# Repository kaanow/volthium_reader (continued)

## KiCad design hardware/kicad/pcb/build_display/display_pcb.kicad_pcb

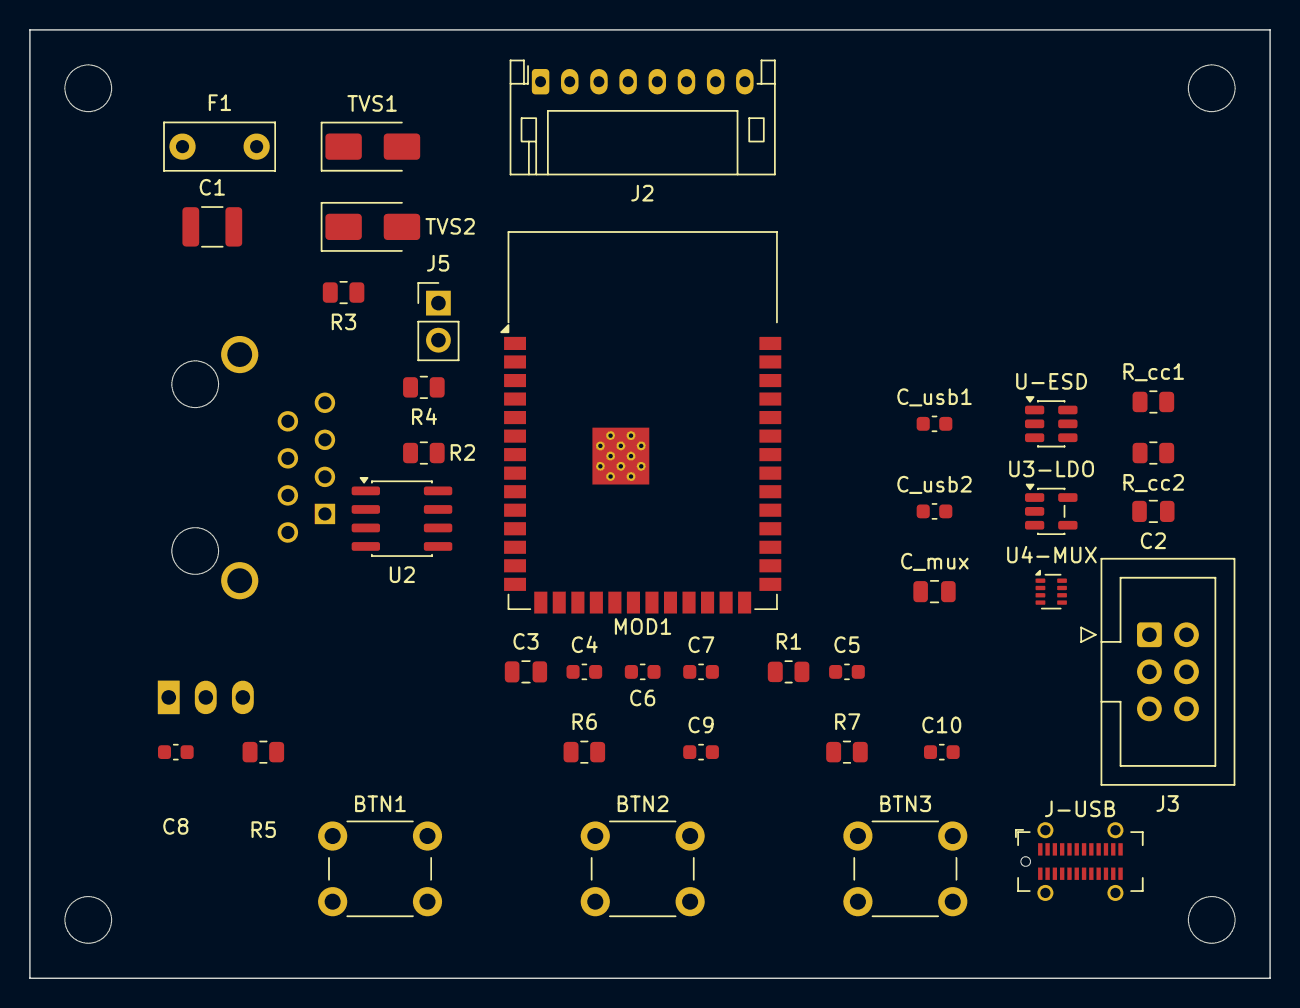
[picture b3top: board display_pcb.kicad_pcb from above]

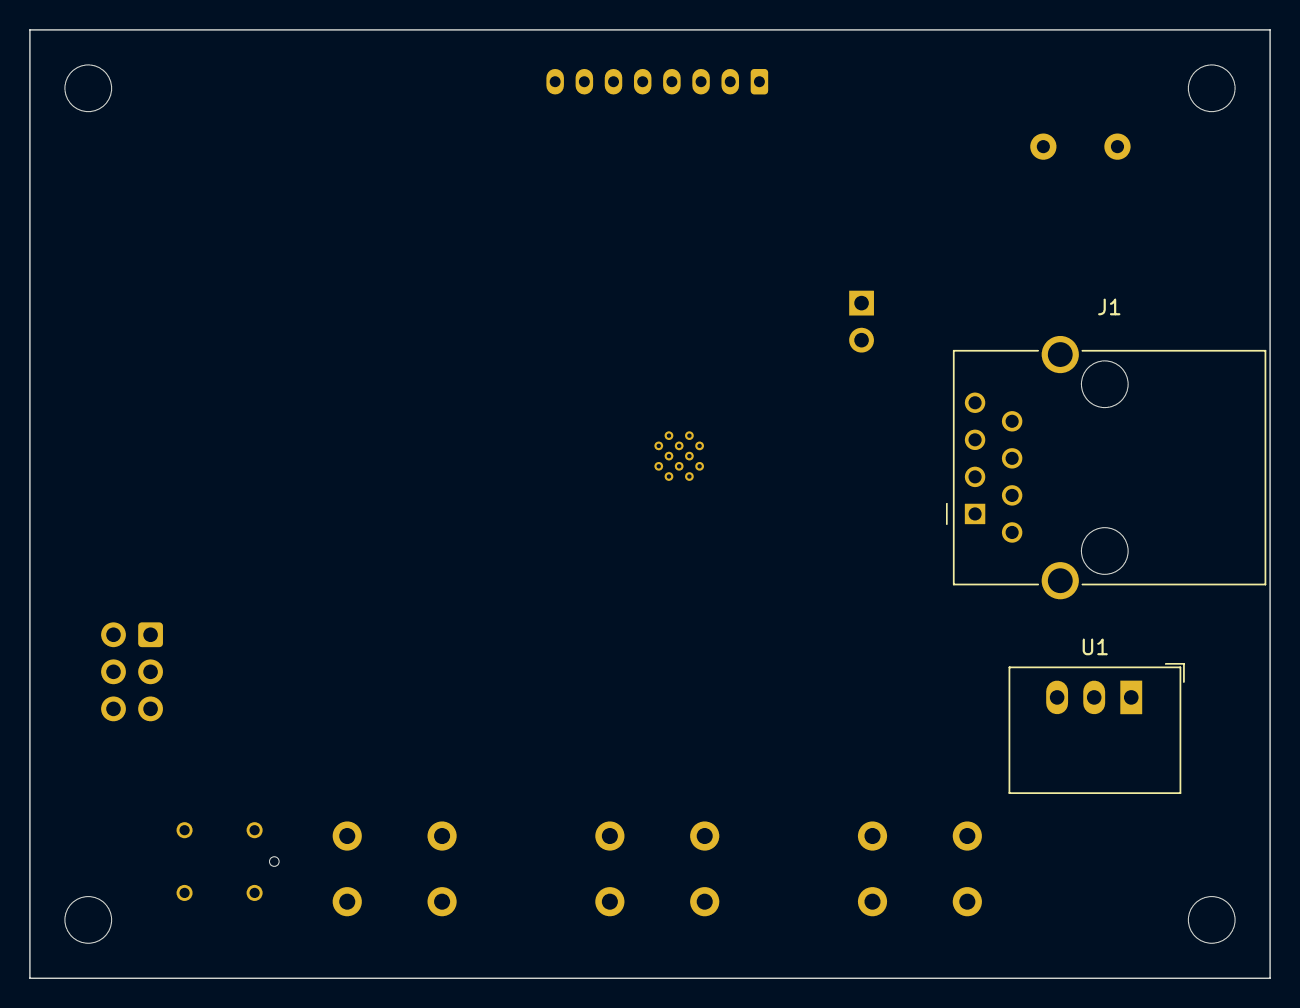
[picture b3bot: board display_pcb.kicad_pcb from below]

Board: 2 copper layers, 85.0 x 65.0 mm, 43 parts (2 on the bottom side), 31 nets, no tracks yet.

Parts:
BTN1, BTN2, BTN3: 6x6 tall-actuator; SW_PUSH_6mm_H13mm
C1: 22µF 25V; C_1210_3225Metric
C2, C3: 10µF; C_0805_2012Metric
C4, C7, C8, C9, C10: 100nF; C_0603_1608Metric
C5, C6: 1µF; C_0603_1608Metric
C_mux: 47µF; C_0805_2012Metric
C_usb1, C_usb2: 1µF; C_0603_1608Metric
F1: MF-R025; Fuse_Bourns_MF-R025_THT_P5.08mm
H1, H2, H3, H4: M3; MountingHole_3.2mm_M3
J1: Wurth_615008145521; J_Wurth_WR-MJ_615008145521
J2: JST_S8B-PH-K-S; JST_PH_S8B-PH-K_1x08_P2.00mm_Horizontal
J3: ESP-Prog; IDC-Header_2x03_P2.54mm_Vertical
J5: TERM; PinHeader_1x02_P2.54mm_Vertical
J-USB: USB4115-03-C; USB_C_Receptacle_GCT_USB4115-03-C
MOD1: ESP32-S3-WROOM-1-N16R8; ESP32-S3-WROOM-1_HSvia0.3_NoAntKeepout
R1: 10k; R_0805_2012Metric
R2: 120; R_0805_2012Metric
R3, R4: 330; R_0805_2012Metric
R5, R6, R7: 1M; R_0805_2012Metric
R_cc1, R_cc2: 5.1k; R_0805_2012Metric
TVS1: SMAJ15A-13-F; D_SMA
TVS2: SMAJ12CA-13-F; D_SMA
U1: R-78E3.3-0.5; Converter_DCDC_RECOM_R-78E-0.5_THT
U2: THVD1400DR; SOIC-8_3.9x4.9mm_P1.27mm
U3-LDO: AP2112K-3.3; SOT-23-5
U4-MUX: TPS2116DRLR; SOT-583-8
U-ESD: USBLC6-2SC6Y; SOT-23-6

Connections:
BOOT: J3.6, MOD1.27
BTN1_IN: BTN1.1, C8.1, MOD1.20, R5.2
BTN2_IN: BTN2.1, C9.1, MOD1.21, R6.2
BTN3_IN: BTN3.1, C10.1, MOD1.22, R7.2
DBG_RXD: J3.5, MOD1.36
DBG_TXD: J3.3, MOD1.37
EPD_BUSY: J2.8, MOD1.12
EPD_CS: J2.5, MOD1.5
EPD_DC: J2.6, MOD1.6
EPD_RST: J2.7, MOD1.7
GND: BTN1.2, BTN2.2, BTN3.2, C1.2, C2.2, C3.1, C4.1, C5.2, C6.2, C7.2, C8.2, C9.2, C10.2, C_mux.2, C_usb1.2, C_usb2.2, J1.6, J1.7, J1.8, J2.2, J3.4, J-USB.A1, J-USB.A12, J-USB.B1, J-USB.B12, J-USB.SH, MOD1.1, MOD1.40, MOD1.41, R4.2, R_cc1.2, R_cc2.2, TVS1.1, U1.2, U2.5, U3-LDO.2, U4-MUX.1, U-ESD.2
MCU_EN: C5.1, J3.1, MOD1.3, R1.2
unnamed: J5.1, R2.2
unnamed: J-USB.A5, R_cc1.1
unnamed: J-USB.B5, R_cc2.1
unnamed: C_usb2.1, U3-LDO.5, U4-MUX.3, U4-MUX.4, U4-MUX.5
RS485_A: J1.4, R2.1, R3.2, TVS2.2, U2.6
RS485_B: J1.5, J5.2, R4.1, TVS2.1, U2.7
RS485_DE: MOD1.38, U2.3
RS485_DI: MOD1.10, U2.4
RS485_RO: MOD1.11, U2.1
RS485_nRE: MOD1.8, U2.2
SPI_MOSI: J2.3, MOD1.18
SPI_SCK: J2.4, MOD1.17
USB_DM: J-USB.A7, J-USB.B7, MOD1.13, U-ESD.3
USB_DP: J-USB.A6, J-USB.B6, MOD1.14, U-ESD.1
V3V3: C3.2, C4.2, C6.1, C7.1, C_mux.1, J2.1, J3.2, MOD1.2, R1.1, R3.1, R5.1, R6.1, R7.1, U2.8, U4-MUX.2, U4-MUX.7
V3V3_REG: C2.1, U1.3, U4-MUX.6
V12_CAT5E: F1.1, J1.1, J1.2, J1.3
V12_PROT: C1.1, F1.2, TVS1.2, U1.1
VBUS: C_usb1.1, J-USB.A4, J-USB.A9, J-USB.B4, J-USB.B9, U3-LDO.1, U3-LDO.3, U-ESD.5

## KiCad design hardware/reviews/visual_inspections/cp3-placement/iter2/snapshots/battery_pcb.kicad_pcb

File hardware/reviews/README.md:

# `hardware/reviews/` — checkpoint review packets

Each PCB-design checkpoint produces a review packet here. Reviewers
(human or agent) start from the packet, follow links into the design
docs, and post findings as comments / commits / PR suggestions.

> **The standing standard is [`SOP.md`](SOP.md)** — the distilled gates,
> principles, and tooling every checkpoint must satisfy, forward-looking and
> free of the incident history. Read it before starting any CP. Role
> playbooks: [`DESIGNER.md`](DESIGNER.md), [`REVIEWER.md`](REVIEWER.md).

| File                            | Phase                | Status     |
|---------------------------------|----------------------|------------|
| `cp1_design_baseline.md`         | Design baseline      | **in review (re-opened, D18/D19)** |
| `cp2_schematic_capture.md`       | Schematic capture    | not started (next) |
| `cp3_placement.md`               | Footprint placement (battery) | not started |
| `cp4_display_placement.md`       | Footprint placement (display) | not started |
| `cp5_routing_drc.md`             | Routing + DRC        | not started |
| `cp6_fab_ready.md`               | Fab-ready package    | not started |

> **Note (2026-06-18):** CP1 was re-opened (decisions.md **D18**) after the
> engineering-correctness gate (D17) found CP1/CP2 architecture defects that
> had ridden to "CP6 fab-ready". The **prior CP2–CP6 review packets** (and
> the CP6 visual-inspection crops) describe board work built on the
> pre-D19 schematics and are **superseded** — they now live in
> [`archive/`](archive/) for history. New CP2+ packets will be written
> fresh against the corrected D19 design.

## What a review packet contains

Each packet is a single markdown file with:

1. **Status banner** — checkpoint name, date opened, current state
2. **What changed since the last checkpoint** — diff summary (commits, file list)
3. **What to look at** — pointers into the design docs + KiCad files,
   with the specific questions to evaluate
4. **Known unknowns / open decisions** — questions Claude is asking the
   reviewer to settle
5. **Success criteria** — what the reviewer needs to see to mark this
   checkpoint passed
6. **Reviewer findings** — appended by the reviewer; iterates until
   findings are resolved

## How to drive a review cycle

1. Claude commits the work and writes the packet
2. User triggers the reviewer (separate agent or human)
3. Reviewer appends findings to the packet
4. Claude addresses findings; updates packet with responses
5. Cycle continues until reviewer marks checkpoint passed
6. Next checkpoint begins

The reviewer is expected to read the packet only, not chase down design
decisions across the repo unless flagged. Claude's job is to make the
review packet self-contained.

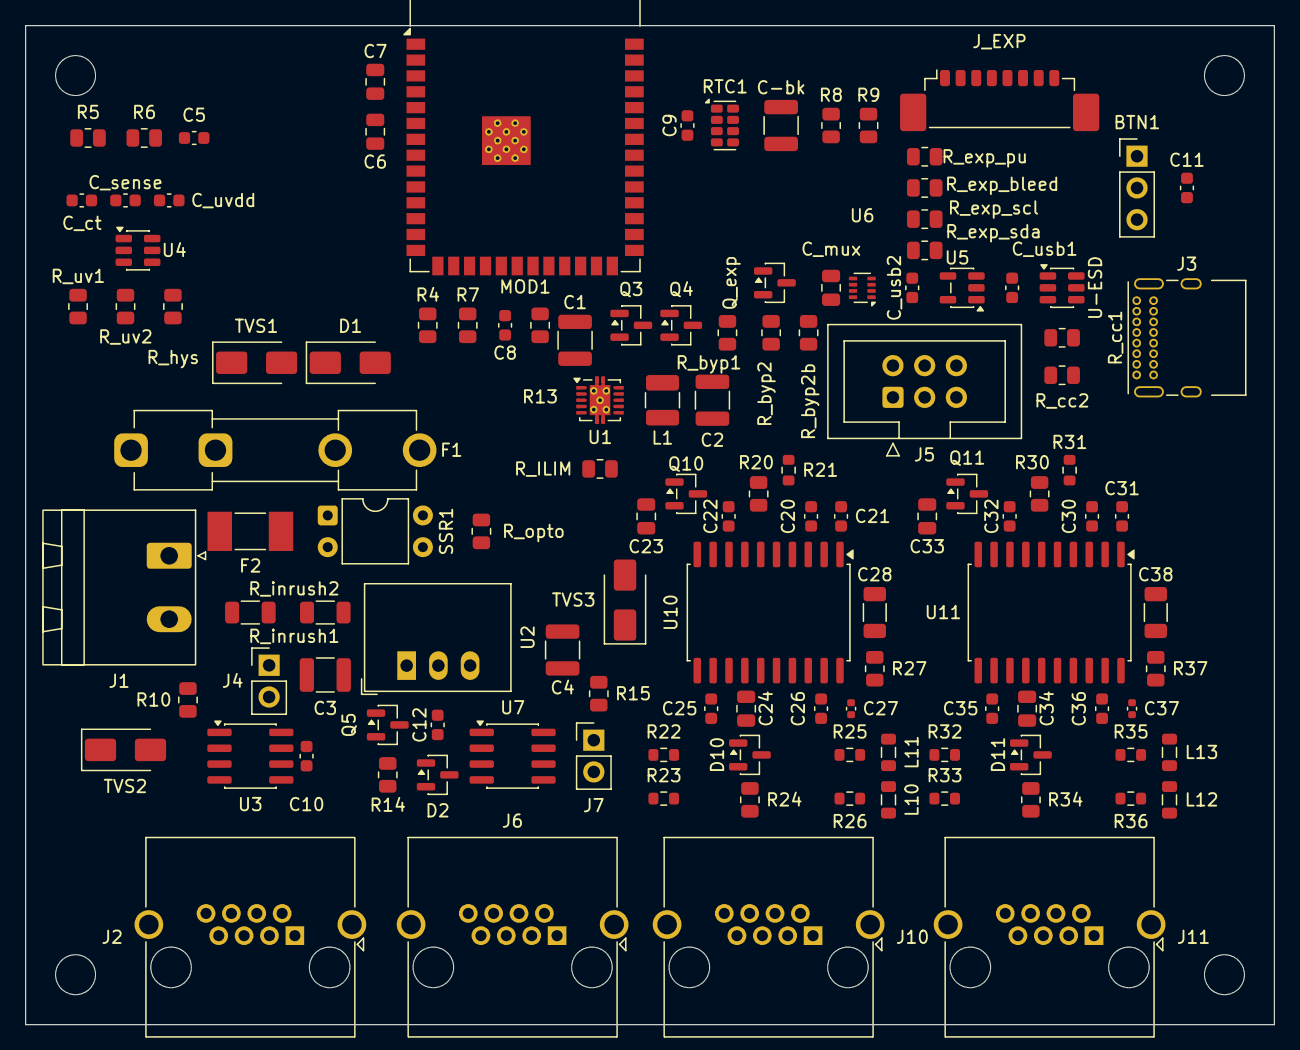
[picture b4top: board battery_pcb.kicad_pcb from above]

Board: 2 copper layers, 100.0 x 80.0 mm, 127 parts (0 on the bottom side), 84 nets, no tracks yet.

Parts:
BTN1: C&K_8125SHZBE; PinHeader_1x03_P2.54mm_Vertical
C1: 22µF 100V; C_1210_3225Metric
C2: 47µF 25V; C_1210_3225Metric
C3: 3.3µF 100V; C_1210_3225Metric
C4: 22µF 25V; C_1210_3225Metric
C5, C9, C10, C11, C12: 100nF; C_0603_1608Metric
C6, C23, C24, C33, C34: 10µF; C_0805_2012Metric
C7: 100nF; C_0805_2012Metric
C8: 1µF; C_0603_1608Metric
C20, C22, C25, C26, C30, C32, C35, C36: 0.1µF; C_0603_1608Metric
C21, C31: 0.01µF; C_0603_1608Metric
C27, C37: 0.01µF; C_0402_1005Metric
C28, C38: 1nF 1kV; C_1206_3216Metric
C-bk: 22mF; C_1210_3225Metric
C_ct: 10nF; C_0603_1608Metric
C_mux: 47µF; C_0805_2012Metric
C_sense: 1nF; C_0603_1608Metric
C_usb1, C_usb2: 1µF; C_0603_1608Metric
C_uvdd: 100nF; C_0603_1608Metric
D1: SS26; D_SMA
D2: DNP (F03); SOT-23
D10, D11: SM712; SOT-23
F1: 1A T; Fuseholder_Clip-5x20mm_Keystone_3517_Inline_P23.11x6.76mm_D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
F2: 80mA; Fuse_Littelfuse-NANO2-451_453
H1, H2, H3, H4: M3; MountingHole_3.2mm_M3
J1: Phoenix_MSTBA_2,5-2-G-5,08; PhoenixContact_MSTBA_2,5_2-G-5,08_1x02_P5.08mm_Horizontal
J2, J6, J10, J11: Amphenol_RJHSE-5380; RJ45_Amphenol_RJHSE5380
J3: USB-C 2.0; USB_C_Receptacle_GCT_USB4085
J4, J7: TERM; PinHeader_1x02_P2.54mm_Vertical
J5: ESP-Prog; IDC-Header_2x03_P2.54mm_Vertical
J_EXP: Molex_PicoBlade_53398-0871; Molex_PicoBlade_53398-0871_1x08-1MP_P1.25mm_Vertical
L1: 4.7µH; L_1210_3225Metric
L10, L11, L12, L13: 600Ω 2A; L_0805_2012Metric
MOD1: ESP32-S3-WROOM-1-N16R8; ESP32-S3-WROOM-1_HSvia0.3
Q3, Q4: 2N7002; SOT-23
Q5, Q10, Q11: NTR4171P; SOT-23
Q_exp: NTR4171P; SOT-23
R4, R6, R14, R20, R30: 100k; R_0805_2012Metric
R5: 1.2M; R_0805_2012Metric
R7: 10k; R_0805_2012Metric
R8, R9: 4.7k; R_0805_2012Metric
R10, R15, R24, R34: 120; R_0805_2012Metric
R13: 1M; R_0805_2012Metric
R21, R31: 1k; R_0603_1608Metric
R22, R23, R32, R33: 10; R_0603_1608Metric
R25, R26, R35, R36: 560; R_0603_1608Metric
R27, R37: 0; R_0805_2012Metric
RTC1: RV-3028-C7; MicroCrystal_C7_SON-8_1.5x3.2mm_P0.9mm
R_ILIM: 56.2k; R_0805_2012Metric
R_byp1, R_byp2: 100k; R_0805_2012Metric
R_byp2b: 1M; R_0805_2012Metric
R_cc1, R_cc2: 5.1k; R_0805_2012Metric
R_exp_bleed: 10k; R_0805_2012Metric
R_exp_pu: 100k; R_0805_2012Metric
R_exp_scl: 4.7k; R_0805_2012Metric
R_exp_sda: 4.7k; R_0805_2012Metric
R_hys: 11.5M; R_0805_2012Metric
R_inrush1, R_inrush2: 75; R_1206_3216Metric
R_opto: 330; R_0805_2012Metric
R_uv1: 5.16M; R_0805_2012Metric
R_uv2: 100k; R_0805_2012Metric
SSR1: AQY212EH; DIP-4_W7.62mm
TVS1: SMAJ33CA; D_SMA
TVS2: SMAJ12CA; D_SMA
TVS3: SMAJ15A; D_SMA
U1: LM5166YDRCR; Texas_S-PVSON-N10_ThermalVias
U2: R-78HB12-0.5; Converter_DCDC_RECOM_R-78E-0.5_THT
U3: THVD1400DR; SOIC-8_3.9x4.9mm_P1.27mm
U4: TPS3808G01DBVR; SOT-23-6
U5: AP2112K-3.3; SOT-23-5
U6: TPS2116DRLR; SOT-583-8
U7: TCAN332DR; SOIC-8_3.9x4.9mm_P1.27mm
U10, U11: ADM2587EBRWZ; SOIC-20W_7.5x12.8mm_P1.27mm
U-ESD: USBLC6-2SC6Y; SOT-23-6

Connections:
BOOT: J5.6, MOD1.27
BTN_OVERRIDE: BTN1.2, C11.1, MOD1.7, R13.2
BUS_A1: J10.7, R22.1, R24.1, R25.1, U10.13, U10.18
BUS_A2: J11.7, R32.1, R34.1, R35.1, U11.13, U11.18
BUS_B1: J10.8, R23.1, R24.2, R26.1, U10.15, U10.17
BUS_B2: J11.8, R33.1, R34.2, R36.1, U11.15, U11.17
CAN_PWR: MOD1.35, Q5.1, R14.2
CAN_RXD: MOD1.34, U7.4
CAN_TXD: MOD1.33, U7.1
CH1_PWR: MOD1.22, Q10.1, R20.1
CH2_PWR: MOD1.32, Q11.1, R30.1
DBG_RXD: J5.5, MOD1.36
DBG_TXD: J5.3, MOD1.37
EXP_3V3: J_EXP.2, Q_exp.3, R_exp_bleed.1, R_exp_scl.1, R_exp_sda.1
EXP_AIO1: J_EXP.5, MOD1.15
EXP_AIO2: J_EXP.6, MOD1.5
EXP_DIO3: J_EXP.7, MOD1.31
EXP_PWR_EN: MOD1.20, Q_exp.1, R_exp_pu.2
EXP_SCL: J_EXP.4, MOD1.19, R_exp_scl.2
EXP_SDA: J_EXP.3, MOD1.18, R_exp_sda.2
GND: BTN1.1, C1.2, C2.2, C3.2, C4.2, C5.2, C6.1, C7.1, C8.2, C9.1, C10.2, C11.2, C12.2, C20.2, C21.2, C22.2, C23.2, C28.1, C30.2, C31.2, C32.2, C33.2, C38.1, C-bk.2, C_ct.2, C_mux.2, C_sense.2, C_usb1.2, C_usb2.2, C_uvdd.1, D2.3, J1.2, J2.6, J2.7, J2.8, J2.SH, J3.A1, J3.A12, J3.B1, J3.B12, J3.SH, J5.4, J6.SH, J_EXP.1, J_EXP.8, MOD1.1, MOD1.40, MOD1.41, Q4.2, R4.2, R6.2, RTC1.5, RTC1.8, R_ILIM.2, R_byp2b.2, R_cc1.2, R_cc2.2, R_exp_bleed.2, R_uv2.2, SSR1.2, TVS1.1, TVS3.1, U1.5, U1.10, U1.11, U2.2, U3.5, U4.2, U5.2, U6.1, U7.2, U10.1, U10.3, U10.5, U10.9, U10.10, U11.1, U11.3, U11.5, U11.9, U11.10, U-ESD.2
GND2_DCDC1: C24.2, C25.2, C28.2, L11.1, U10.11, U10.14
GND2_DCDC2: C34.2, C35.2, C38.2, L13.1, U11.11, U11.14
I2C_SCL: MOD1.17, R9.2, RTC1.3
I2C_SDA: MOD1.12, R8.2, RTC1.4
ISO_BUS_GND1: C26.2, C27.2, D10.3, J10.SH, L11.2, R26.2, R27.1, U10.16, U10.20
ISO_BUS_GND2: C36.2, C37.2, D11.3, J11.SH, L13.2, R36.2, R37.1, U11.16, U11.20
MCU_EN: C8.1, J5.1, MOD1.3, Q3.3, R7.2
unnamed: D1.2, F1.2
unnamed: F2.1, SSR1.4
unnamed: J3.A5, R_cc1.1
unnamed: J3.B5, R_cc2.1
unnamed: J4.1, R10.2
unnamed: J7.1, R15.2
unnamed: Q3.1, Q4.3, R_byp1.2
unnamed: Q4.1, R_byp2.2, R_byp2b.1
unnamed: C12.1, Q5.3, U7.3
unnamed: C-bk.1, RTC1.6
unnamed: R_inrush1.1, SSR1.3
unnamed: R_inrush1.2, R_inrush2.1
unnamed: R_opto.2, SSR1.1
unnamed: R_ILIM.1, U1.3
unnamed: L1.1, U1.1
unnamed: C_ct.1, U4.4
unnamed: C_sense.1, R_hys.1, R_uv1.2, R_uv2.1, U4.5
unnamed: C_usb2.1, U5.5, U6.3, U6.4, U6.5
unnamed: D2.2, J6.5, R15.1, U7.7
unnamed: D2.1, J6.4, J7.2, U7.6
unnamed: R21.2, U10.7
unnamed: R31.2, U11.7
PWR_EN: MOD1.4, R4.1, R_opto.1
RS485B_DE1: MOD1.21, U10.6
RS485B_DE2: MOD1.25, U11.6
RS485B_DI1: MOD1.6, R21.1
RS485B_DI2: MOD1.23, R31.1
RS485B_RO1: MOD1.9, U10.4
RS485B_RO2: MOD1.24, U11.4
RS485_A: J2.4, R10.1, TVS2.2, U3.6
RS485_B: J2.5, J4.2, TVS2.1, U3.7
RS485_DE: MOD1.38, U3.3
RS485_DI: MOD1.10, U3.4
RS485_RO: MOD1.11, U3.1
RS485_nRE: MOD1.8, U3.2
TVA1: D10.1, R22.2
TVA2: D11.1, R32.2
TVB1: D10.2, R23.2
TVB2: D11.2, R33.2
USB_DM: J3.A7, J3.B7, MOD1.13, U-ESD.3
USB_DP: J3.A6, J3.B6, MOD1.14, U-ESD.1
UVLO_RESET: Q3.2, R_hys.2, U4.1
V3V3: C6.2, C7.2, C9.2, C10.1, C_mux.1, C_uvdd.2, J5.2, MOD1.2, Q5.2, Q10.2, Q11.2, Q_exp.2, R7.1, R8.1, R9.1, R13.1, R14.1, R20.2, R30.2, RTC1.7, R_byp1.1, R_exp_pu.1, U3.8, U4.6, U6.2, U6.7
V3V3_BUCK: C2.1, L1.2, U1.8, U6.6
V12_CAT5E: C4.1, J2.1, J2.2, J2.3, TVS3.2, U2.3
V24_FUSED: C1.1, D1.1, F2.2, R5.1, R_uv1.1, TVS1.2, U1.2, U1.7
V24_RAW: F1.1, J1.1
V24_SENSE: C5.1, MOD1.39, R5.2, R6.1
V24_SW: C3.1, R_inrush2.2, U2.1
VBUS: C_usb1.1, J3.A4, J3.A9, J3.B4, J3.B9, R_byp2.1, U5.1, U5.3, U-ESD.5
VCC1: C20.1, C21.1, C22.1, C23.1, Q10.3, U10.2, U10.8
VCC2: C30.1, C31.1, C32.1, C33.1, Q11.3, U11.2, U11.8
V_ISOIN1: C26.1, C27.1, L10.2, R25.2, U10.19
V_ISOIN2: C36.1, C37.1, L12.2, R35.2, U11.19
V_ISOOUT1: C24.1, C25.1, L10.1, U10.12
V_ISOOUT2: C34.1, C35.1, L12.1, U11.12
